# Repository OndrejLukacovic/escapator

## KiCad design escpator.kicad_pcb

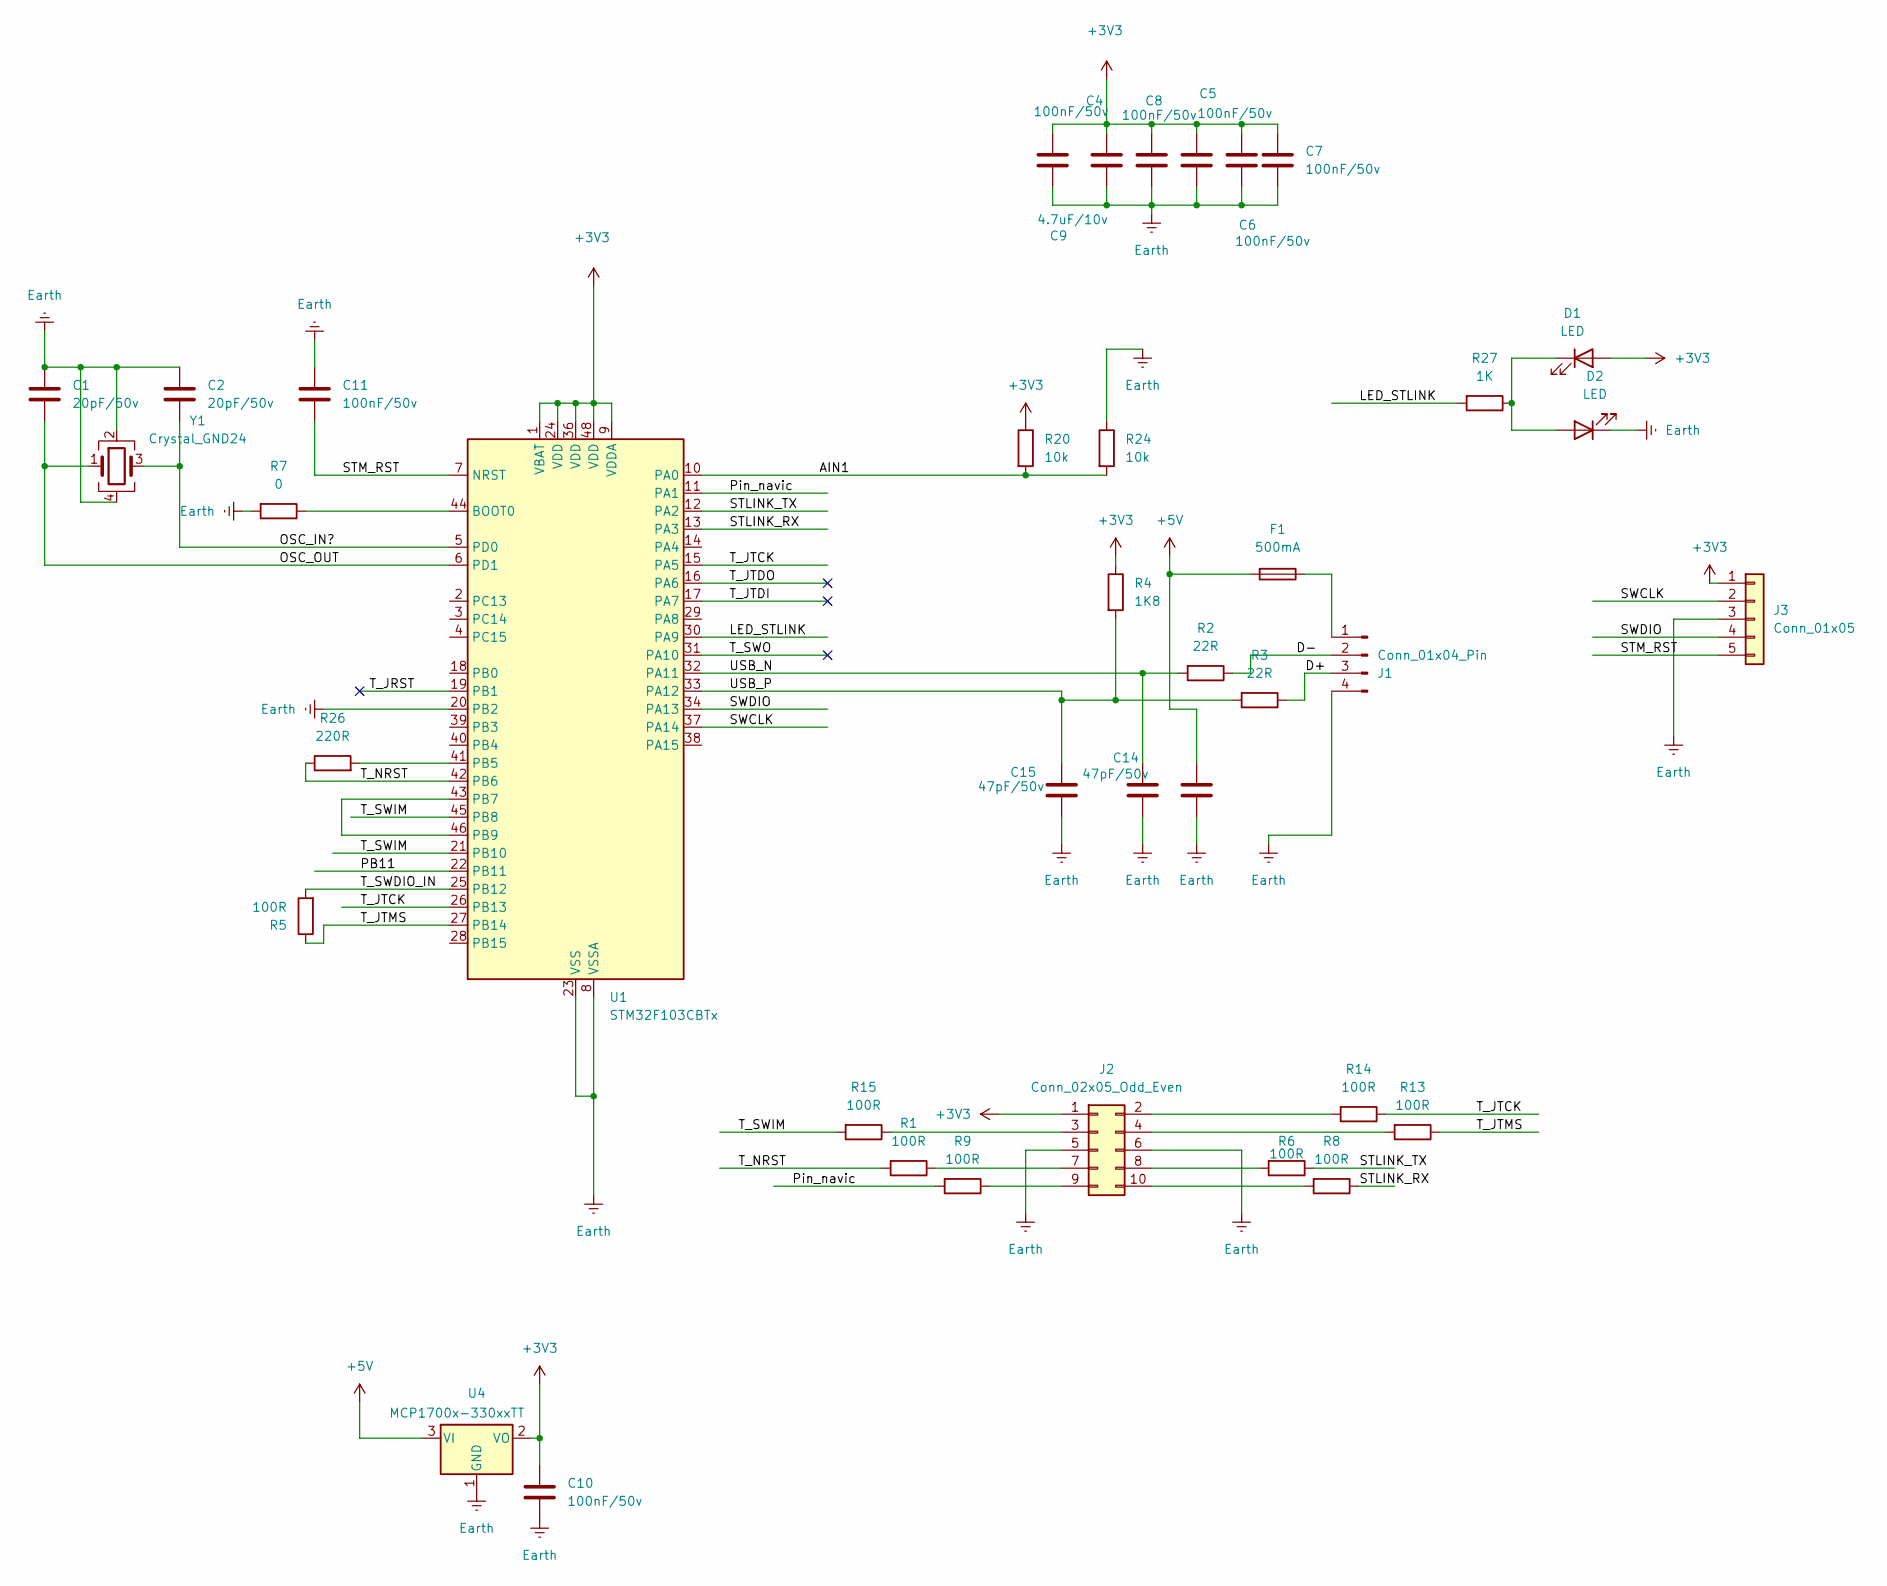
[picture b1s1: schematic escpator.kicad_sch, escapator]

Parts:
C1, C2: 20pF/50v; C_0603_1608Metric; LCSC Part # C105621
C3, C4, C5, C6, C7, C8, C10, C11: 100nF/50v; C_0603_1608Metric; LCSC Part # C14663
C9: 4.7uF/10v; C_0603_1608Metric; LCSC Part # C1705
C14, C15: 47pF/50v; C_0603_1608Metric; LCSC Part # C1671
D1, D2: LED; LED_0603_1608Metric; LCSC Part # C965799
F1: 500mA; R_1206_3216Metric
J1: Conn_01x04_Pin; USB_A_PCB_traces_small
J2: Conn_02x05_Odd_Even; Untitled
J3: Conn_01x05; Untitled_3
R1, R5, R6, R8, R9, R13, R14, R15: 100R; R_0603_1608Metric
R2, R3: 22R; R_0603_1608Metric; LCSC Part # C23345
R4: 1K8; R_0603_1608Metric; LCSC Part # C2906979
R7: 0; R_0603_1608Metric
R20, R24: 10k; R_0603_1608Metric
R26: 220R; R_0603_1608Metric; LCSC Part # C22962
R27: 1K; R_0603_1608Metric
U1: STM32F103CBTx; LQFP-48_7x7mm_P0.5mm; LCSC Part # C8304
U4: MCP1700x-330xxTT; SOT-23
Y1: Crystal_GND24; Crystal_SMD_3225-4Pin_3.2x2.5mm_HandSoldering; LCSC Part # C7275084

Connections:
+3V3: C4.1, C5.1, C6.1, C7.1, C8.1, C9.1, C10.1, D1.2 (A), J2.1, J3.1, R4.1, R20.1, U1.1 (VBAT), U1.9 (VDDA), U1.24 (VDD), U1.36 (VDD), U1.48 (VDD), U4.2 (VO)
+5V: C3.1, F1.2, U4.3 (VI)
/AIN1: R20.2, R24.2, U1.10 (PA0)
/D+: J1.3, R3.1
/D-: J1.2, R2.1
/LED_STLINK: R27.2, U1.30 (PA9)
/OSC_IN?: C2.2, U1.5 (PD0), Y1.3
/OSC_OUT: C1.2, U1.6 (PD1), Y1.1
/PB11: U1.22 (PB11)
/Pin_navic: R9.2, U1.11 (PA1)
/STLINK_RX: R8.1, U1.13 (PA3)
/STLINK_TX: R6.1, U1.12 (PA2)
/STM_RST: C11.2, J3.5, U1.7 (NRST)
/SWCLK: J3.2, U1.37 (PA14)
/SWDIO: J3.4, U1.34 (PA13)
/T_JRST: U1.19 (PB1)
/T_JTCK: R14.1, U1.15 (PA5), U1.26 (PB13)
/T_JTDI: U1.17 (PA7)
/T_JTDO: U1.16 (PA6)
/T_JTMS: R5.1, R13.1, U1.27 (PB14)
/T_NRST: R1.2, R26.1, U1.42 (PB6)
/T_SWDIO_IN: R5.2, U1.25 (PB12)
/T_SWIM: R15.2, U1.21 (PB10), U1.45 (PB8)
/T_SWO: U1.31 (PA10)
/USB_N: C14.1, R2.2, U1.32 (PA11)
/USB_P: C15.1, R3.2, R4.2, U1.33 (PA12)
Earth: C1.1, C2.1, C3.2, C4.2, C5.2, C6.2, C7.2, C8.2, C9.2, C10.2, C11.1, C14.2, C15.2, D2.1 (K), J1.4, J2.5, J2.6, J3.3, R7.2, R24.1, U1.8 (VSSA), U1.20 (PB2), U1.23 (VSS), U1.35 (VSS), U1.47 (VSS), U4.1 (GND), Y1.2, Y1.4
unnamed: D1.1 (K), D2.2 (A), R27.1
unnamed: F1.1, J1.1
unnamed: J2.2, R14.2
unnamed: J2.3, R15.1
unnamed: J2.4, R13.2
unnamed: J2.7, R1.1
unnamed: J2.8, R6.2
unnamed: J2.9, R9.1
unnamed: J2.10, R8.2
unnamed: R7.1, U1.44 (BOOT0)
unnamed: R26.2, U1.41 (PB5)
unnamed: U1.43 (PB7), U1.46 (PB9)

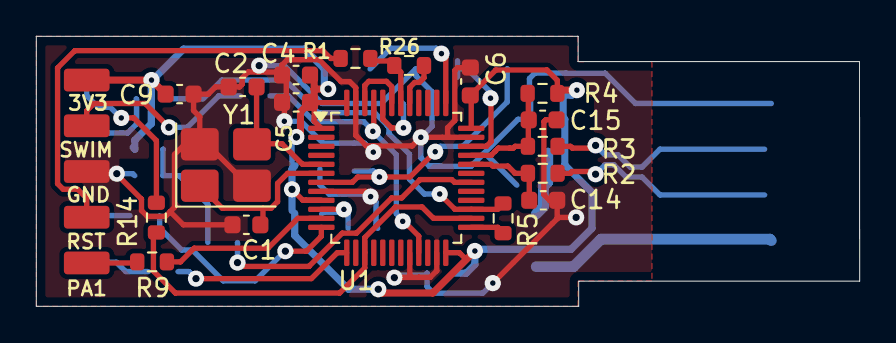
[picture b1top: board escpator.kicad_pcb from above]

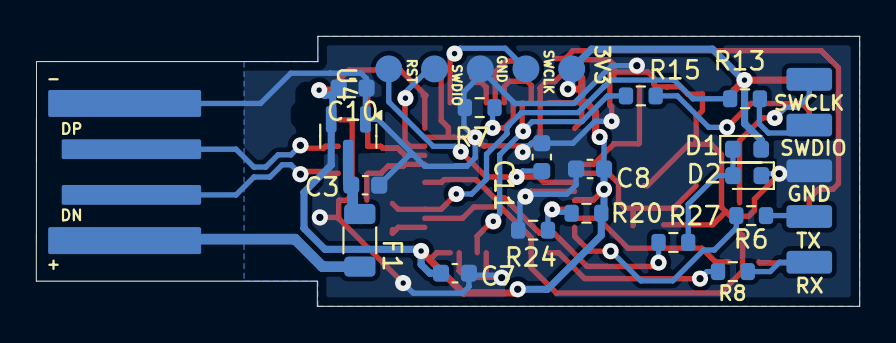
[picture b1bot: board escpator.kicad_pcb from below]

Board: 2 copper layers, 45.7 x 15.0 mm, 38 parts (19 on the bottom side), 34 nets.

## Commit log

2025-07-24 first
2025-07-24 second
2025-07-25 presun LED plus otoceni USB
2025-07-28 changedpins
2025-07-28 flipped USB connector
2025-07-28 flip LED
2025-07-28 aaaaa
2025-07-28 mon28jul1400
2025-07-30 snadfinalverze
2025-07-31 panelizace_a_gbr
2025-08-05 prazdnacommitmessage
